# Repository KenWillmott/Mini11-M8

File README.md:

# Mini11-M8
MC68HC11A1 MCU based SBC

## IMPORTANT! This project is deprecated. It's superceded by this device:
https://github.com/KenWillmott/Mini11-M8E

This project is based on hardware and software developed here:
https://github.com/EtchedPixels/Mini11

# Overview
This is a 10cm * 10cm PCB with an MC68HC11A1 processor. It uses only traditional through hole PCB construction and MSI glue logic in the 74HC line. It does not have any programmable logic device other than the usual EEPROM. There is one exception, the reset controller is an SMD device. This is because of a noticeable cost/availability problem with through hole type reset controllers. To interface with additional peripherals, the board follows M8 sytem outline and mounting hole dimensions, and is equipped with a full bus interface that will connect with the M8 series of peripheral expansion PCB's available on this hosting.

The processor itself has a lot of built in features that make a self contained computer easier to make. The serial connection can connect to a host computer or some other device. The processor can support a TF memory card directly with software driving the built in SPI. That gives it a disk. To complement that there is 512kb of non volatile memory, battery backed up. Any 32k bank of this memory can be assigned to either the upper or lower 32k of the CPU memory map, by writing to the memory paging control latch. This essentially makes all the memory selectively available to the CPU.

The main memory is made non-volatile using a DS1210 NVRAM controller IC. An option is provided for either 128kb or 512kb of memory. Either one is a single IC. There is provision for either an on board or external battery, and also an auxiliary battery for additional protection or to allow hot swapping batteries.

# Memory Map
## Hardware
- 0000-7FFF  Bank 0 NVRAM
- 8000-EFFF  Bank 1 NVRAM
- F000-F03F  CPU control registers
- F040-F0FF  Internal RAM
- F100-F3FF  Bank 1 NVRAM
- F400-F7FF  Expansion Bus Device Select
- F800-FFFF  EPROM/EEPROM (read) / Memory Paging Register (write)
## Software
(current)
- 0000-EC00 dual bank general purpose memory
- EF80  stack
- EFC4-EFFF CPU vector jump table
- F800-FB5F Boot code
- FF80  I/O vector table
- FFD6-FFFF CPU vectors
## Operation
Currently, the system boots from the 2k ROM space. It sets up some system variables and then attempts to boot from SD. If a disk is found, it will load the first sector of disk into RAM and then run it. If SD is not used, the 2k block below the highest block can be programmed with a stand alone monitor. The upper and lower half of upper 4k of EEPROM is configured with a jumper on the PCB, so that a choice of boot routines can be made. The monitor is duplicated with the boot firmware, so is available for support in case the disk does not operate.

The CPU vectors in high ROM are copied into a vector table in RAM so that they can be redirected. simple serial I/O routines are in ROM, and can be used by applications by referencing the table in ROM where they are combined.

Memory banking is simple. The upper 4 bits of the memory latch select one of sixteen 32kb blocs from the 512kb main memory, that will appear in the upper 32k of CPU memory. Similarly, the lower 4 bits of the memory latch select an independent 32k bank from main memory, which appears in the lower 32k of CPU memory.
# Connectors
## J2 SPI/SD
Connects to the MCU SPI pins, mimics the common pinout of an SD/TF card adapter module (such as often used with Arduino). The module must have its own 3.3V/5V signal voltage translation on board. Many modules don't have that and can't tolerate 5V from the MCU
## J1 Serial
Typical TX/RX/VCC/GND connections usually to a USB to serial adapter module.
## J3 Parallel I/O
MCU Port A pins PA0-PA6 are presented at a connector (PA7 is used for an additional SD chip select)
## J6 Analog
MCU ADC inputs PE0-PE3, VCC and GND
# Jumpers
## JP4 Boot select
- 0: monitor
- 1: boot from SD card
## J7 BAT1
Place a jumper across two of the three pins to select:
- int: connects internal battery to the NVRAM controller
- ext: use to connect an external backup battery (3.0V) or a jumper to disable the NVRAM.
## J8 BAT2
Optionally connect an secondary, auxiliary backup battery. If this is powered, the on board battery may be changed without any data loss. Place a jumper if no battery is connected.
## JP3 512/128
- 512: use 512kb IC such as AS6C4008
- 128: use 128kb IC such as AS6C1008
## RES SW
provision for an external reset switch. Note that the MCU reset circuit is not common drain, it is a CMOS driven voltage level. Thus any reset signal must not be applied to the MCU/bus RESET signal line, only to the internal/external reset switch circuit that controls the reset controller IC.
## MODA, MODB
These are MCU mode control pins. They are held high with pull up resistors so are left open in normal operation.

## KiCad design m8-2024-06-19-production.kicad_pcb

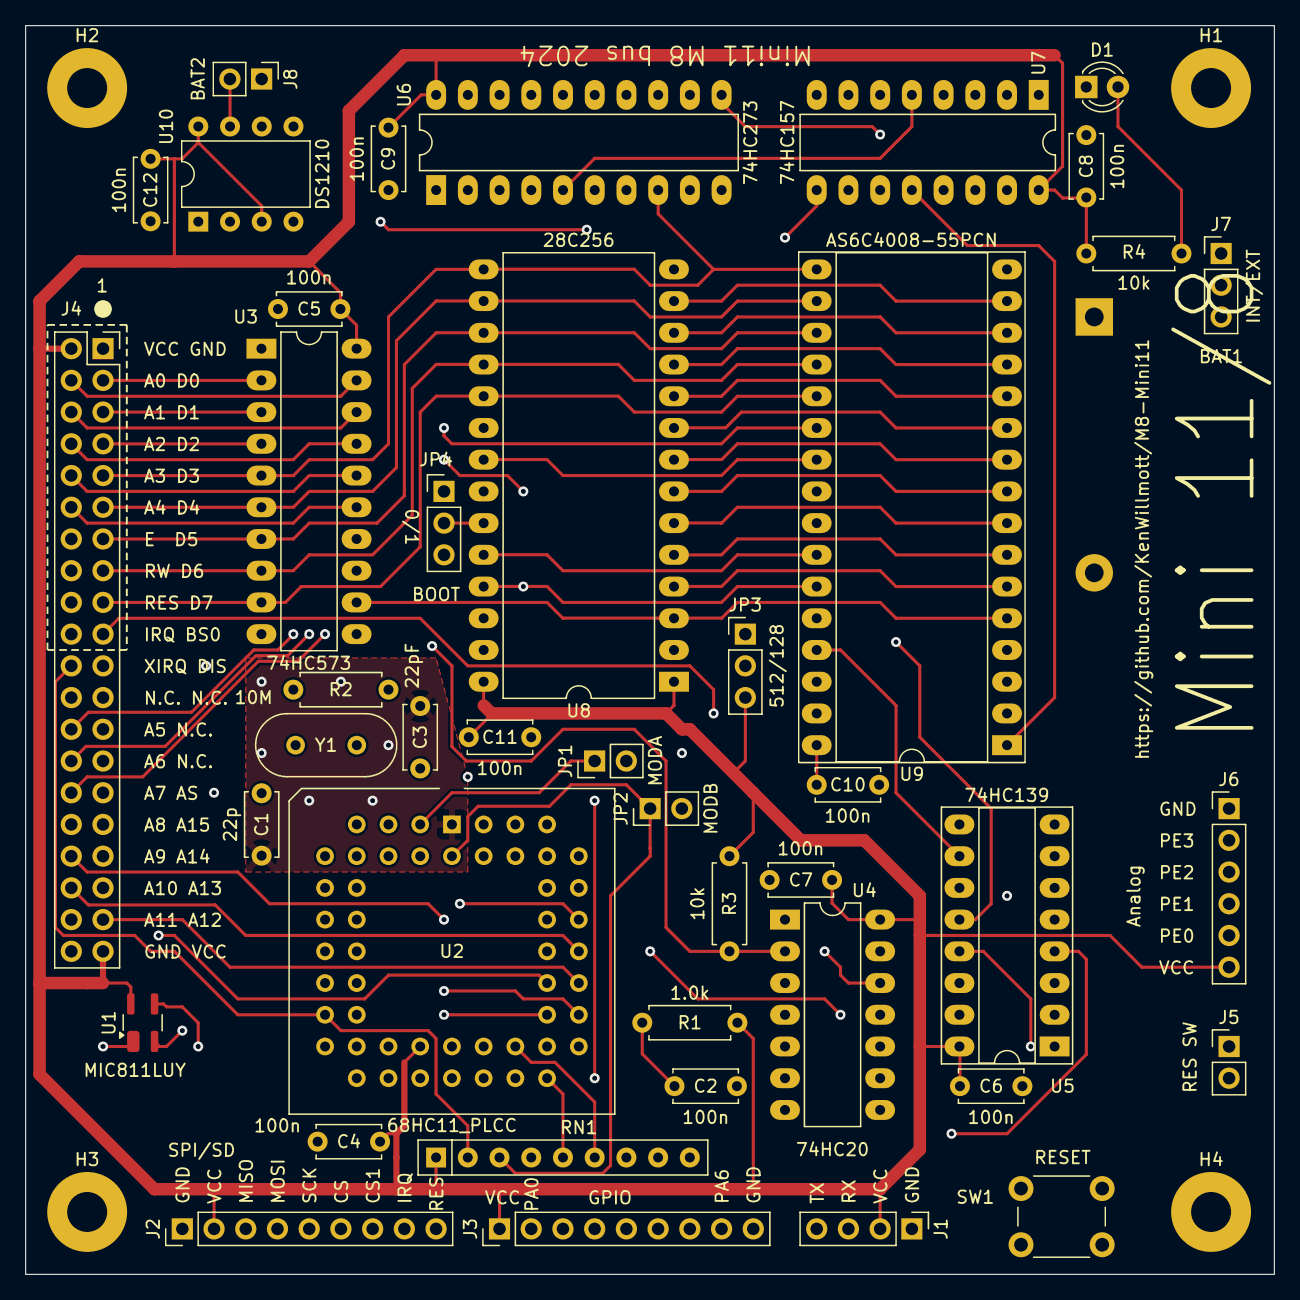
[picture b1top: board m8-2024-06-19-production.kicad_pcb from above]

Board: 4 copper layers, 100.0 x 100.0 mm, 47 parts (1 on the bottom side), 85 nets.

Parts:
BT1: CR2032; BatteryHolder_Keystone_107_1x23mm
C1: 22p; C_Disc_D5.0mm_W2.5mm_P5.00mm
C2, C4, C5, C6, C7, C8, C9, C10, C11, C12: 100n; C_Disc_D5.0mm_W2.5mm_P5.00mm
C3: 22pF; C_Disc_D5.0mm_W2.5mm_P5.00mm
D1: PWR; LED_D3.0mm
H1, H2, H3, H4: MountingHole_Pad; MountingHole_3.2mm_M3_Pad
J1: Serial; PinHeader_1x04_P2.54mm_Vertical
J2: SD Memory; PinHeader_1x09_P2.54mm_Vertical
J3: MCU I/O; PinHeader_1x09_P2.54mm_Vertical
J4: Conn_02x20_Odd_Even; PinSocket_2x20_P2.54mm_Vertical
J5: Conn_01x02_Pin; PinHeader_1x02_P2.54mm_Vertical
J6: Analog; PinHeader_1x06_P2.54mm_Vertical
J7: BAT1; PinHeader_1x03_P2.54mm_Vertical
J8: BAT2; PinHeader_1x02_P2.54mm_Vertical
JP1: MODA; PinHeader_1x02_P2.54mm_Vertical
JP2: MODB; PinHeader_1x02_P2.54mm_Vertical
JP3: 512/128; PinHeader_1x03_P2.54mm_Vertical
JP4: BOOT; PinHeader_1x03_P2.54mm_Vertical
R1: 1.0k; R_Axial_DIN0207_L6.3mm_D2.5mm_P7.62mm_Horizontal
R2: 10M; R_Axial_DIN0207_L6.3mm_D2.5mm_P7.62mm_Horizontal
R3, R4: 10k; R_Axial_DIN0207_L6.3mm_D2.5mm_P7.62mm_Horizontal
RN1: 10K; R_Array_SIP9
SW1: RESET; SW_PUSH_6mm_H4.3mm
U1: MIC811LUY; SOT-143_Handsoldering
U2: 68HC11_PLCC; PLCC-52_THT-Socket
U3: 74HC573; DIP-20_W7.62mm_LongPads
U4: 74HC20; DIP-14_W7.62mm_LongPads
U5: 74HC139; DIP-16_W7.62mm_Socket_LongPads
U6: 74HC273; DIP-20_W7.62mm_LongPads
U7: 74HC157; DIP-16_W7.62mm_LongPads
U8: 28C256; DIP-28_W15.24mm_LongPads
U9: AS6C4008-55PCN; DIP-32_W15.24mm_Socket_LongPads
U10: DS1210; DIP-8_W7.62mm
Y1: 7.3728 MHz; Crystal_HC18-U_Vertical

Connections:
/A0: J4.4, U3.19 (Q0), U8.10 (A0), U9.12 (A0)
/A1: J4.6, U3.18 (Q1), U8.9 (A1), U9.11 (A1)
/A2: J4.8, U3.17 (Q2), U8.8 (A2), U9.10 (A2)
/A3: J4.10, U3.16 (Q3), U8.7 (A3), U9.9 (A3)
/A4: J4.12, U3.15 (Q4), U8.6 (A4), U9.8 (A4)
/A5: J4.26, U3.14 (Q5), U8.5 (A5), U9.7 (A5)
/A6: J4.28, U3.13 (Q6), U8.4 (A6), U9.6 (A6)
/A7: J4.30, U3.12 (Q7), U8.3 (A7), U9.5 (A7)
/A8: J4.32, U2.42 (A8/PB0), U8.25 (A8), U9.27 (A8)
/A9: J4.34, U2.41 (PB1), U8.24 (A9), U9.26 (A9)
/A10: J4.36, U2.40 (PB2), U5.2 (A0), U8.21 (A10), U9.23 (A10)
/A11: J4.38, JP3.1 (A), U2.39 (PB3), U5.3 (A1)
/A12: J4.37, U2.38 (PB4), U4.13, U9.4 (A12)
/A13: J4.35, U2.37 (PB5), U4.12, U9.28 (A13)
/A14: J4.33, U2.36 (PB6), U4.10, U9.3 (A14)
/A15: J4.31, U2.35 (A15/PB7), U4.9, U7.1 (S)
/CS: J2.6, U2.25 (PD5)
/CS1: J2.7, U2.27 (PA1/PA7)
/D0: J4.3, U2.9 (AD0/PC0), U3.2 (D0), U6.3 (D0), U8.11 (D0), U9.13 (DQ0)
/D1: J4.5, U2.10 (AD1/PC1), U3.3 (D1), U6.4 (D1), U8.12 (D1), U9.14 (DQ1)
/D2: J4.7, U2.11 (AD2/PC2), U3.4 (D2), U6.7 (D2), U8.13 (D2), U9.15 (DQ2)
/D3: J4.9, U2.12 (AD3/PC3), U3.5 (D3), U6.8 (D3), U8.15 (D3), U9.17 (DQ3)
/D4: J4.11, U2.13 (AD4/PC4), U3.6 (D4), U6.13 (D4), U8.16 (D4), U9.18 (DQ4)
/D5: J4.13, U2.14 (AD5/PC5), U3.7 (D5), U6.14 (D5), U8.17 (D5), U9.19 (DQ5)
/D6: J4.15, U2.15 (AD6/PC6), U3.8 (D6), U6.17 (D6), U8.18 (D6), U9.20 (DQ6)
/D7: J4.17, U2.16 (AD7/PC7), U3.9 (D7), U6.18 (D7), U8.19 (D7), U9.21 (DQ7)
/Decode/RAM/~ROMIO: U4.8, U5.1 (E), U5.13 (A1)
/Decode/Y0: U6.12 (Q4), U7.3 (I1a)
/Decode/Y1: U6.15 (Q5), U7.6 (I1b)
/Decode/Y2: U6.16 (Q6), U7.10 (I1c)
/Decode/Y3: U6.19 (Q7), U7.13 (I1d)
/Decode/Z0: U6.2 (Q0), U7.2 (I0a)
/Decode/Z1: U6.5 (Q1), U7.5 (I0b)
/Decode/Z2: U6.6 (Q2), U7.11 (I0c)
/Decode/Z3: U6.9 (Q3), U7.14 (I0d)
/Decode/~LATWR: U5.12 (O0), U6.11 (Cp)
/Decode/~RAMRD: U5.9 (O3), U9.24 (OE#)
/Decode/~RAMWR: U5.10 (O2), U9.29 (WE#)
/Decode/~ROMEN: U5.11 (O1), U8.22 (~OE)
/MISO: J2.3, U2.22 (PD2)
/MODA: JP1.1 (A), RN1.8 (R7), U2.3 (MODA)
/MODB: JP2.1 (A), RN1.3 (R2), U2.2 (MODB)
/MOSI: J2.4, U2.23 (PD3)
/PA3: J3.5, U2.31 (OC5/PA3)
/PA4: J3.6, U2.30 (OC4/PA4)
/PA5: J3.7, U2.29 (OC3/PA5)
/PA6: J3.8, U2.28 (OC2/PA6)
/SCK: J2.5, U2.24 (PD4)
/TX: J1.4, U2.21 (PD1/TX)
/bus/DIS: J4.21, R3.2, U4.2
AS: J4.29, U2.4 (AS), U3.11 (Load)
BSEL1*: J4.19, U4.4, U5.5 (O1)
E: J4.14, U2.5 (E), U4.1
GND: BT1.2 (-), C1.2, C2.2, C3.2, C4.2, C5.2, C6.2, C7.2, C8.2, C9.2, C10.2, C11.2, C12.2, D1.1 (K), H1.1, H2.1, H3.1, H4.1, J1.1, J2.1, J3.9, J4.1, J4.40, J5.1, J6.1, J7.1, J8.1, JP1.2 (B), JP2.2 (B), JP4.1 (A), SW1.1 (A), U1.1 (GND), U2.1 (VSS), U2.51 (VRL), U3.1 (OE), U3.10 (GND), U4.7 (GND), U5.8 (GND), U6.10 (GND), U7.8 (GND), U7.15 (E), U8.14 (GND), U8.20 (~CS), U9.16 (VSS), U10.4 (GND), U10.5 (~CE)
IRQ*: J2.8, J4.20, RN1.7 (R6), U2.19 (IRQ)
unnamed: BT1.1 (+), J7.3
unnamed: D1.2 (A), R4.2
unnamed: J5.2, SW1.2 (B), U1.3 (~MR)
unnamed: J6.2, U2.49 (PE3)
unnamed: J6.3, U2.47 (PE2)
unnamed: J6.4, U2.45 (PE1)
unnamed: J6.5, U2.43 (PE0)
unnamed: J7.2, U10.2 (VBAT1)
unnamed: J8.2, U10.7 (VBAT2)
unnamed: JP3.2 (C), U9.25 (A11)
unnamed: JP4.2 (C), U8.23 (A11)
unnamed: C3.1, R2.2, U2.7 (EXTAL), Y1.2
unnamed: C2.1, R1.2, U2.52 (VRH)
unnamed: C1.1, R2.1, U2.8 (XTAL), Y1.1
unnamed: U4.5, U5.4 (O0)
unnamed: U4.6, U5.15 (E)
unnamed: U7.4 (Za), U9.31 (A15)
unnamed: U7.7 (Zb), U9.2 (A16)
unnamed: U7.9 (Zc), U9.30 (A17)
unnamed: U7.12 (Zd), U9.1 (A18)
unnamed: C10.1, U9.32 (VCC), U10.1 (VCCO)
unnamed: U9.22 (CE#), U10.6 (~CEO)
PA0: J3.2, RN1.4 (R3), U2.34 (IC3/PA0)
PA1: J3.3, RN1.5 (R4), U2.33 (IC2/PA1)
PA2: J3.4, RN1.6 (R5), U2.32 (IC1/PA2)
RES*: J2.9, J4.18, U1.2 (~RESET), U2.17 (RESET), U6.1 (~Mr)
RX: J1.3, RN1.9 (R8), U2.20 (PD0/RX)
R/W*: J4.16, U2.6 (R/W), U5.14 (A0)
VCC: C4.1, C5.1, C6.1, C7.1, C8.1, C9.1, C11.1, C12.1, J1.2, J2.2, J3.1, J4.2, J4.39, J6.6, JP3.3 (B), JP4.3 (B), R1.1, R3.1, R4.1, RN1.1 (common), U1.4 (VCC), U2.26 (VDD), U3.20 (VCC), U4.14 (VCC), U5.16 (VCC), U6.20 (VCC), U7.16 (VCC), U8.1 (A14), U8.2 (A12), U8.26 (A13), U8.27 (~WE), U8.28 (VCC), U10.3 (TOL), U10.8 (VCCI)
XIRQ*: J4.22, RN1.2 (R1), U2.18 (XIRQ)

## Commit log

2024-07-09 Add files via upload
    boot ROM
2024-11-19 EEPROM boot firmware
    EEPROM resident boot and KBUG monitor
